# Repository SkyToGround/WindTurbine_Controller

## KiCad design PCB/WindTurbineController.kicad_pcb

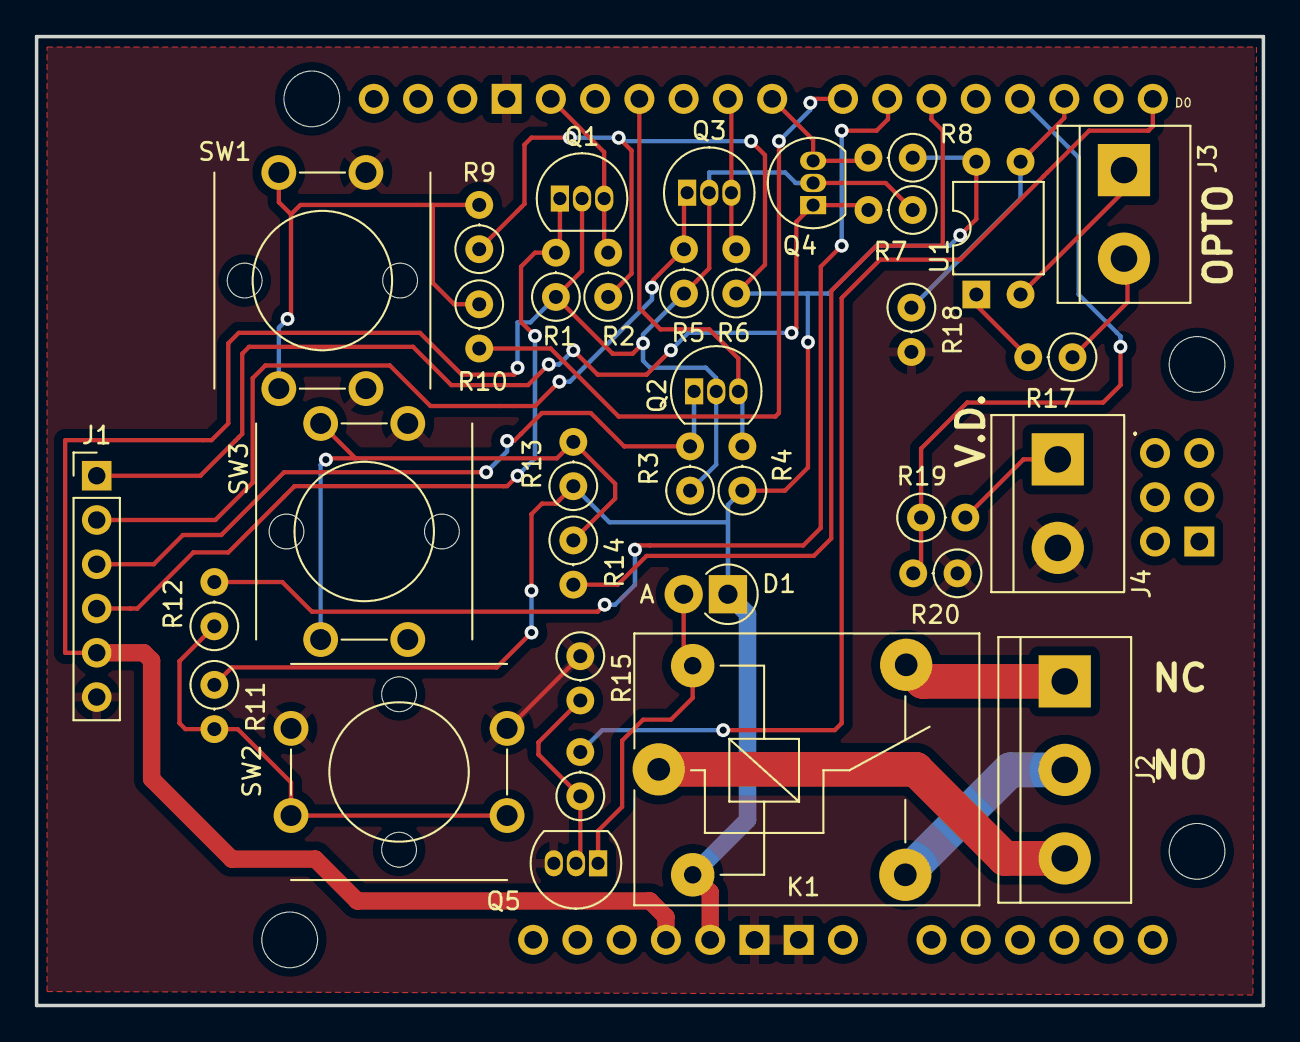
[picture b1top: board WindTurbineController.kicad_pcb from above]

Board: 2 copper layers, 70.4 x 55.6 mm, 36 parts (0 on the bottom side), 29 nets.

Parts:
D1: 1N4001; D_DO-41_SOD81_P2.54mm_Vertical_AnodeUp
J1: Conn_01x06_Male; PinHeader_1x06_P2.54mm_Vertical
J2: Screw_Terminal_01x03; TerminalBlock_bornier-3_P5.08mm
J3, J4: Screw_Terminal_01x02; TerminalBlock_bornier-2_P5.08mm
K1: SANYOU_SRD_Form_C; Relay_SPDT_SANYOU_SRD_Series_Form_C
Q1, Q2, Q3, Q4: 2N7000; TO-92_Inline
Q5: BC337; TO-92_Inline
R1, R2, R3, R4, R5, R6, R7, R8: 10K; R_Axial_DIN0207_L6.3mm_D2.5mm_P2.54mm_Vertical
R9, R11, R13: 12k; R_Axial_DIN0207_L6.3mm_D2.5mm_P2.54mm_Vertical
R10, R12, R14: 220; R_Axial_DIN0207_L6.3mm_D2.5mm_P2.54mm_Vertical
R15: 4k7; R_Axial_DIN0207_L6.3mm_D2.5mm_P2.54mm_Vertical
R16: 470; R_Axial_DIN0207_L6.3mm_D2.5mm_P2.54mm_Vertical
R17, R20: 1k; R_Axial_DIN0207_L6.3mm_D2.5mm_P2.54mm_Vertical
R18: 10k; R_Axial_DIN0207_L6.3mm_D2.5mm_P2.54mm_Vertical
R19: 2k; R_Axial_DIN0207_L6.3mm_D2.5mm_P2.54mm_Vertical
SW1, SW2, SW3: SW_Push; SW_Push_Unknown
U1: PC817; DIP-4_W7.62mm
XA1: Arduino_Uno_Shield

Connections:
+3.3V: J1.5 (VDD), Q1.2 (G), Q2.2 (G), Q3.2 (G), Q4.2 (G), R1.1, R3.1, R5.1, R7.1, XA1.3V3 (3.3V)
+5V: D1.1 (K), K1.2, R2.1, R4.1, R6.1, R8.1, R9.1, R11.1, R13.1, U1.4, XA1.5V1 (5V)
/btn1/btn_in: R10.2, XA1.D7
/btn2/btn_in: R12.2, XA1.D6
/btn3/btn_in: R14.2, XA1.D5
/level_translator_1/3V_IO: J1.4 (SCK), Q1.1 (S), R1.2
/level_translator_1/5V_IO: Q1.3 (D), R2.2, XA1.D13
/level_translator_2/3V_IO: J1.3 (SDA), Q2.1 (S), R3.2
/level_translator_2/5V_IO: Q2.3 (D), R4.2, XA1.D11
/level_translator_3/3V_IO: J1.2 (RES), Q3.1 (S), R5.2
/level_translator_3/5V_IO: Q3.3 (D), R6.2, XA1.D9
/level_translator_4/3V_IO: J1.1 (CD), Q4.1 (S), R7.2
/level_translator_4/5V_IO: Q4.3 (D), R8.2, XA1.D8
GND: J1.6 (GND), J4.2, Q5.3 (E), R15.1, R18.2, R20.1, SW1.2, SW2.2, SW3.2, XA1.GND1 (GND), XA1.GND2 (GND), XA1.GND3 (GND)
unnamed: D1.2 (A), K1.5, Q5.1 (C)
unnamed: J2.1, K1.4
unnamed: J2.2, K1.3
unnamed: J2.3, K1.1
unnamed: J3.1, U1.2
unnamed: J3.2, R17.1
unnamed: J4.1, R19.2
unnamed: Q5.2 (B), R15.2, R16.1
unnamed: R9.2, R10.1, SW1.1
unnamed: R11.2, R12.1, SW2.1
unnamed: R13.2, R14.1, SW3.1
unnamed: R16.2, XA1.D0 (D0_RX0)
unnamed: R17.2, U1.1
unnamed: R18.1, U1.3, XA1.D2 (D2_INT0)
unnamed: R19.1, R20.2, XA1.D3 (D3_INT1)

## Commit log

2023-01-08 Initial commit.
2023-01-08 Change name.
2023-01-09 PCB implemented.
2023-01-09 Kind of working.
2023-01-09 Bug fix.
2023-01-10 Bug fix?
2023-01-23 Final version?
